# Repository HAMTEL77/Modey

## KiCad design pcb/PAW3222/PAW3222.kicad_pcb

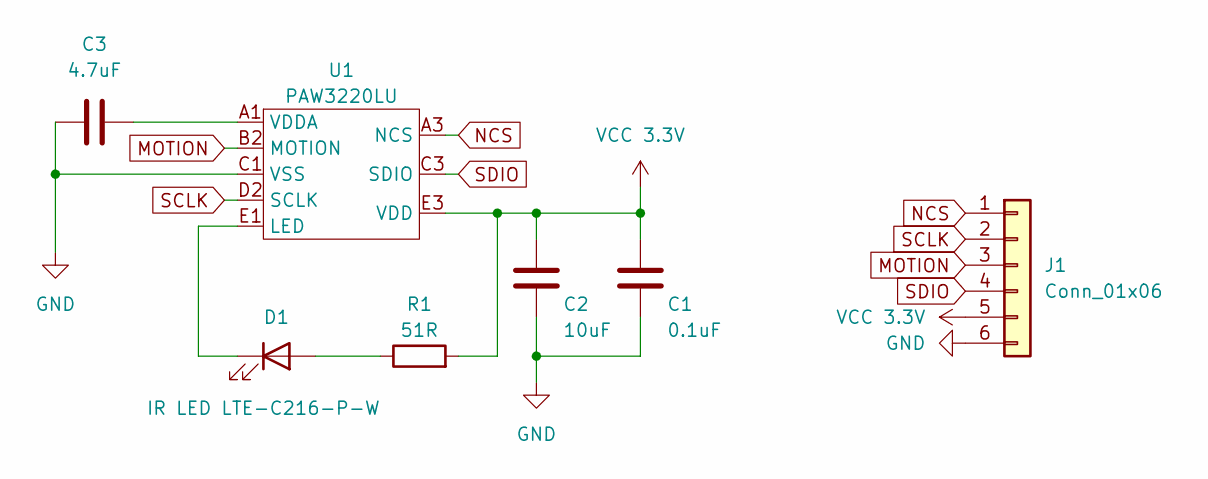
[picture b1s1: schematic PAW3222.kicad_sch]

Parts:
C1: 0.1uF; C_0402_1005Metric
C2: 10uF; C_0402_1005Metric
C3: 4.7uF; C_0402_1005Metric
D1: IR LED LTE-C216-P-W; LTE-C216-P-W; LCSC C2942980
J1: Conn_01x06; CONN_FH19C-6S-0.5SH10_HIR
R1: 51R; R_0402_1005Metric
U1: PAW3220LU; PAW3222LU; LCSC C9900022540

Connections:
GND: C1.2, C2.2, C3.2, J1.6, U1.C1 (VSS)
MOTION: J1.3, U1.B2 (MOTION)
NCS: J1.1, U1.A3 (NCS)
unnamed: D1.2 (A), R1.1
unnamed: D1.1 (K), U1.E1 (LED)
unnamed: C3.1, U1.A1 (VDDA)
SCLK: J1.2, U1.D2 (SCLK)
SDIO: J1.4, U1.C3 (SDIO)
VCC 3.3V: C1.1, C2.1, J1.5, R1.2, U1.E3 (VDD)

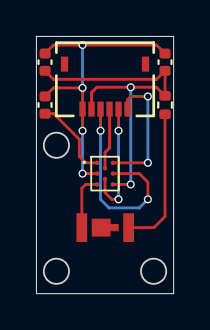
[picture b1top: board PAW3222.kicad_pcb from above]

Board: 2 copper layers, 7.6 x 14.3 mm, 7 parts (0 on the bottom side), 9 nets.

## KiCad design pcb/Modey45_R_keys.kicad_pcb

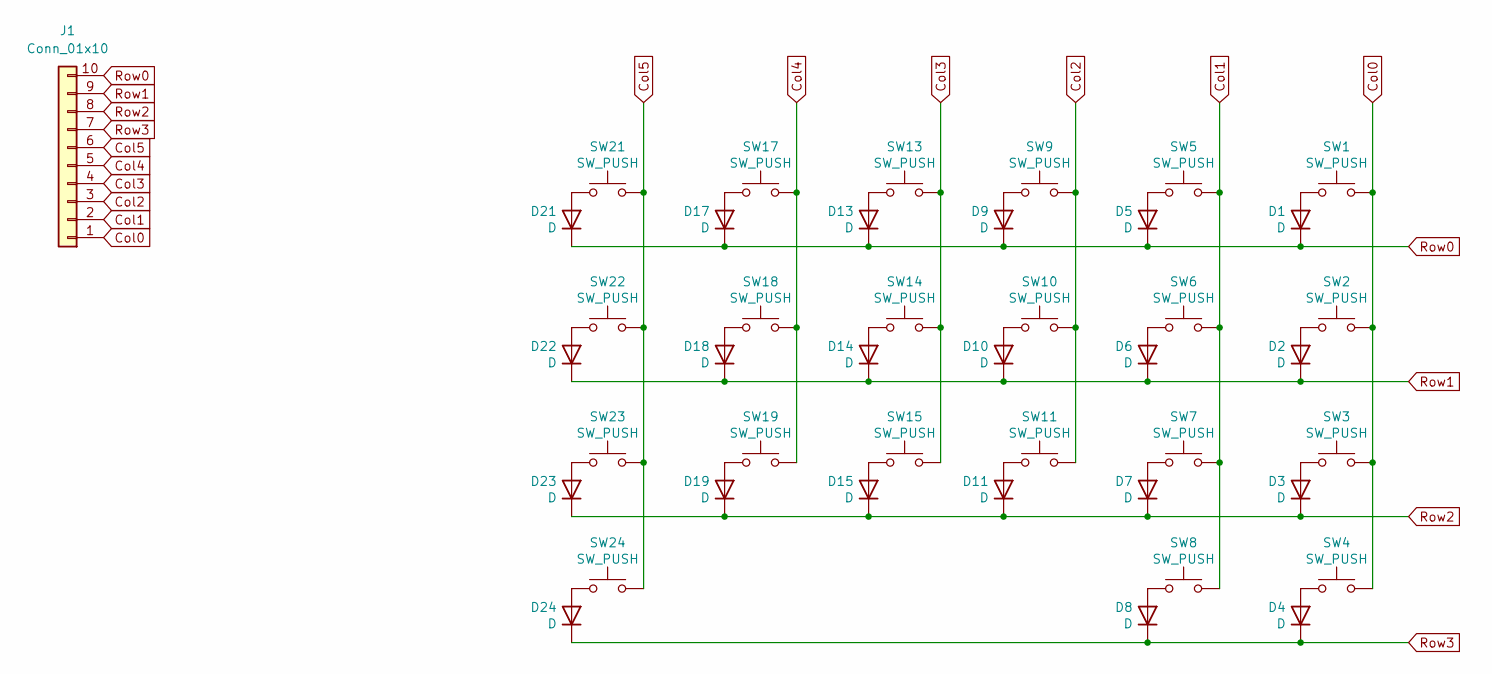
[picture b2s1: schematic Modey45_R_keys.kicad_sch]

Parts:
D1, D2, D3, D4, D5, D6, D7, D8, D9, D10, D11, D13, D14, D15, D17, D18, D19, D21, D22, D23, D24: D; Diode_SMD
J1: Conn_01x10; CONN_FH19C-10S-0.5SH10_HIR
SW1, SW2, SW3, SW4, SW5, SW6, SW7, SW8, SW9, SW10, SW11, SW13, SW14, SW15, SW17, SW18, SW19, SW21, SW22, SW23, SW24: SW_PUSH; SW_Choc

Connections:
Col0: J1.1, SW1.1, SW2.1, SW3.1, SW4.1
Col1: J1.2, SW5.1, SW6.1, SW7.1, SW8.1
Col2: J1.3, SW9.1, SW10.1, SW11.1
Col3: J1.4, SW13.1, SW14.1, SW15.1
Col4: J1.5, SW17.1, SW18.1, SW19.1
Col5: J1.6, SW21.1, SW22.1, SW23.1, SW24.1
unnamed: D1.2 (A), SW1.2
unnamed: D2.2 (A), SW2.2
unnamed: D3.2 (A), SW3.2
unnamed: D4.2 (A), SW4.2
unnamed: D5.2 (A), SW5.2
unnamed: D6.2 (A), SW6.2
unnamed: D7.2 (A), SW7.2
unnamed: D8.2 (A), SW8.2
unnamed: D9.2 (A), SW9.2
unnamed: D10.2 (A), SW10.2
unnamed: D11.2 (A), SW11.2
unnamed: D13.2 (A), SW13.2
unnamed: D14.2 (A), SW14.2
unnamed: D15.2 (A), SW15.2
unnamed: D17.2 (A), SW17.2
unnamed: D18.2 (A), SW18.2
unnamed: D19.2 (A), SW19.2
unnamed: D21.2 (A), SW21.2
unnamed: D22.2 (A), SW22.2
unnamed: D23.2 (A), SW23.2
unnamed: D24.2 (A), SW24.2
Row0: D1.1 (K), D5.1 (K), D9.1 (K), D13.1 (K), D17.1 (K), D21.1 (K), J1.10
Row1: D2.1 (K), D6.1 (K), D10.1 (K), D14.1 (K), D18.1 (K), D22.1 (K), J1.9
Row2: D3.1 (K), D7.1 (K), D11.1 (K), D15.1 (K), D19.1 (K), D23.1 (K), J1.8
Row3: D4.1 (K), D8.1 (K), D24.1 (K), J1.7

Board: 2 copper layers, 43 parts (1 on the bottom side), 31 nets.

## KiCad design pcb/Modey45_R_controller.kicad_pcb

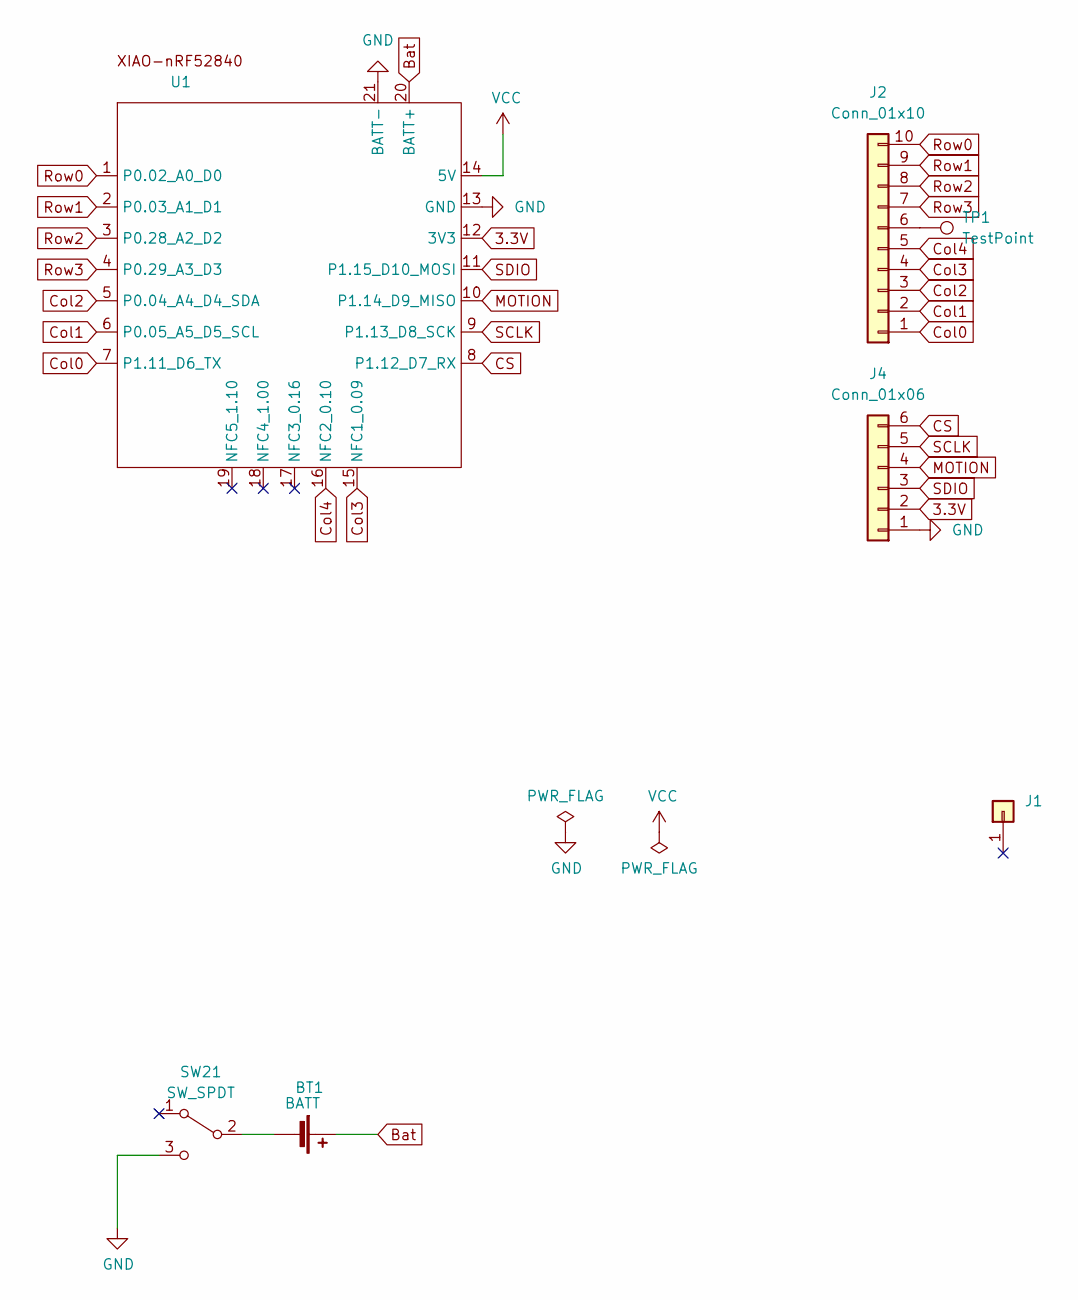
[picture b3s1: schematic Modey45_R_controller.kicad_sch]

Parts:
BT1: BATT; Battery_hole_2pin
J1: Conn_01x01-Connector_Generic; MountingHole_2.2mm_M2
J2: Conn_01x10; CONN_FH19C-10S-0.5SH10_HIR
J4: Conn_01x06; CONN_FH19C-6S-0.5SH10_HIR
SW21: SW_SPDT; MSK-12C02
TP1: TestPoint; TestPoint_THTPad_D1.0mm_Drill0.5mm
U1: XIAO_nRF52840_wBAT_wNFC_1

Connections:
3.3V: J4.2, U1.12 (3V3)
Bat: BT1.1 (+), U1.20 (BATT+)
CS: J4.6, U1.8 (P1.12_D7_RX)
Col0: J2.1, U1.7 (P1.11_D6_TX)
Col1: J2.2, U1.6 (P0.05_A5_D5_SCL)
Col2: J2.3, U1.5 (P0.04_A4_D4_SDA)
Col3: J2.4, U1.15 (NFC1_0.09)
Col4: J2.5, U1.16 (NFC2_0.10)
GND: J4.1, SW21.3 (C), U1.13 (GND), U1.21 (BATT-)
MOTION: J4.4, U1.10 (P1.14_D9_MISO)
unnamed: BT1.2 (-), SW21.2 (B)
unnamed: J2.6, TP1.1
Row0: J2.10, U1.1 (P0.02_A0_D0)
Row1: J2.9, U1.2 (P0.03_A1_D1)
Row2: J2.8, U1.3 (P0.28_A2_D2)
Row3: J2.7, U1.4 (P0.29_A3_D3)
SCLK: J4.5, U1.9 (P1.13_D8_SCK)
SDIO: J4.3, U1.11 (P1.15_D10_MOSI)
VCC: U1.14 (5V)

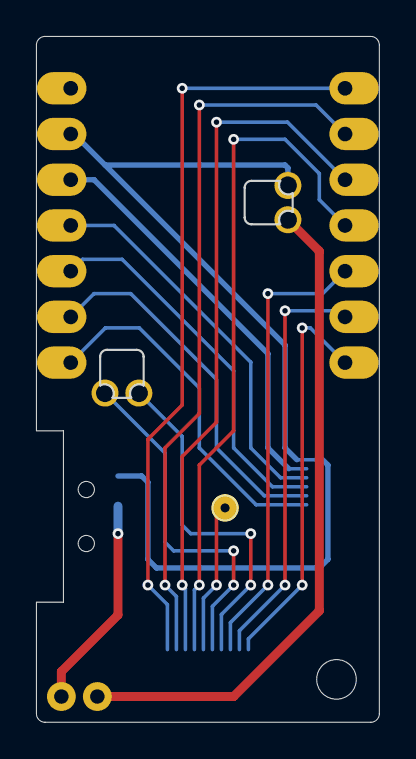
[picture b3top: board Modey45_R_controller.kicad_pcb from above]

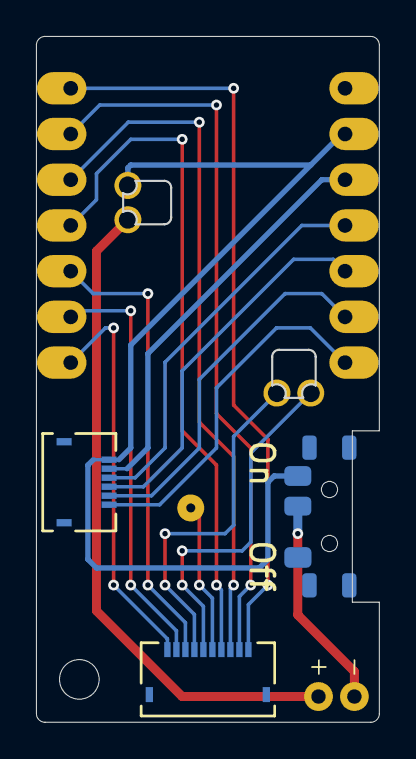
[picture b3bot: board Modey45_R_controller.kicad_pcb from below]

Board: 2 copper layers, 19.0 x 38.1 mm, 7 parts (5 on the bottom side), 18 nets.

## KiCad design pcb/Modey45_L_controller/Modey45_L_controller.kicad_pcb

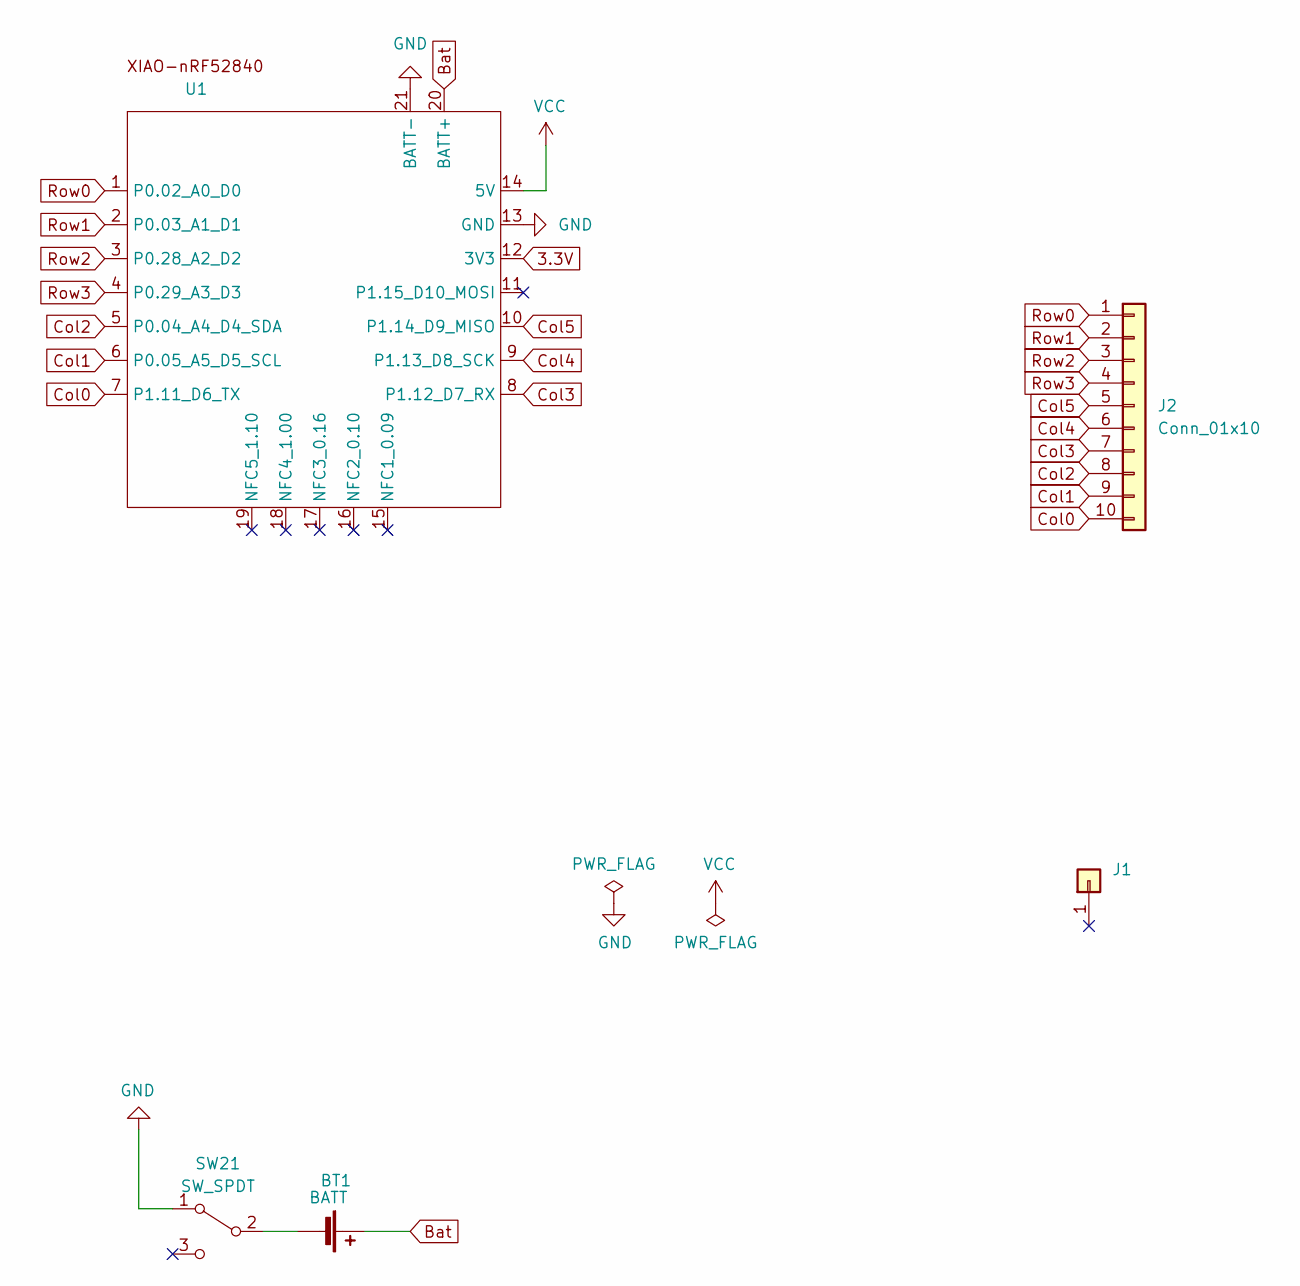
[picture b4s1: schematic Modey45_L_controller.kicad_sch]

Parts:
BT1: BATT; Battery_hole_2pin
J1: Conn_01x01-Connector_Generic; MountingHole_2.2mm_M2
J2: Conn_01x10; CONN_FH19C-10S-0.5SH10_HIR
SW21: SW_SPDT; MSK-12C02
U1: XIAO_nRF52840_wBAT_wNFC_1

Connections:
3.3V: U1.12 (3V3)
Bat: BT1.1 (+), U1.20 (BATT+)
Col0: J2.10, U1.7 (P1.11_D6_TX)
Col1: J2.9, U1.6 (P0.05_A5_D5_SCL)
Col2: J2.8, U1.5 (P0.04_A4_D4_SDA)
Col3: J2.7, U1.8 (P1.12_D7_RX)
Col4: J2.6, U1.9 (P1.13_D8_SCK)
Col5: J2.5, U1.10 (P1.14_D9_MISO)
GND: SW21.1 (A), U1.13 (GND), U1.21 (BATT-)
unnamed: BT1.2 (-), SW21.2 (B)
Row0: J2.1, U1.1 (P0.02_A0_D0)
Row1: J2.2, U1.2 (P0.03_A1_D1)
Row2: J2.3, U1.3 (P0.28_A2_D2)
Row3: J2.4, U1.4 (P0.29_A3_D3)
VCC: U1.14 (5V)

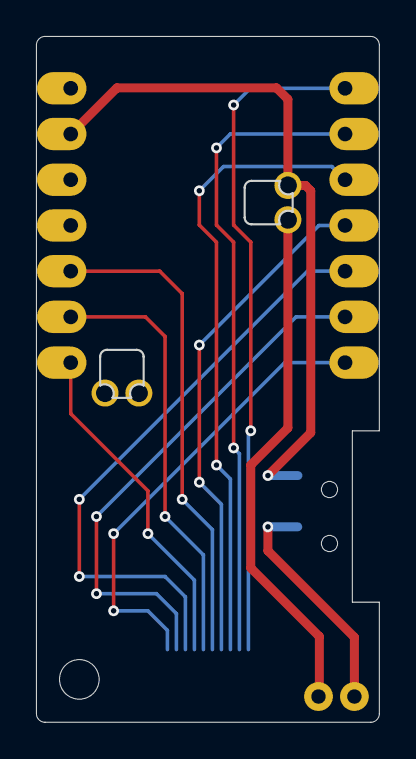
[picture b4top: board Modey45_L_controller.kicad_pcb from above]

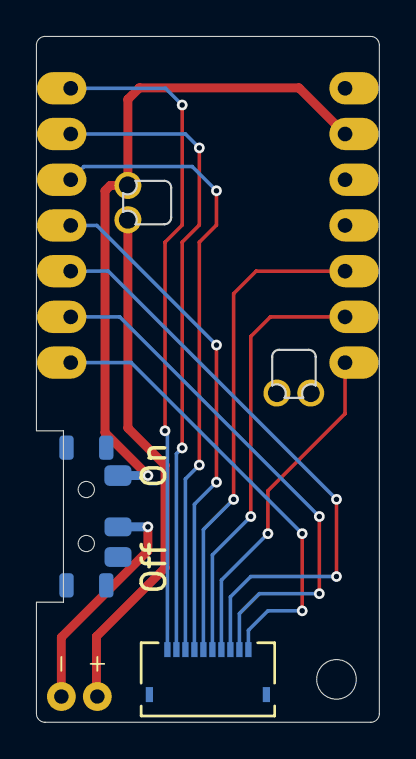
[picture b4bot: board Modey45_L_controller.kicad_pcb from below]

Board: 2 copper layers, 19.0 x 38.1 mm, 5 parts (4 on the bottom side), 13 nets.
